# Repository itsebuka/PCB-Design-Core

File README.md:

# PCB Design Core

A central portfolio repository housing PCB design files, schematic captures, and embedded hardware prototypes. Projects range from custom microcontroller systems to specialized power management boards and discrete logic circuits.

---

## 🚀 Projects Overview

### 1. ESP32-S3 Test Board
* **Description:** Custom hardware evaluation platform designed around the ESP32-S3 microcontroller for IoT prototyping and wireless development.
* **Key Features:**
  * Clean power regulation network for stable MCU operation.
  * Dedicated break-out headers for GPIO, I2C, SPI, and UART peripherals.
  * Optimized 2-layer PCB layout with dedicated ground plane for RF/noise stability.
* **Directory:** [`/ESP32 S3 TESTBOARD`](./ESP32%20S3%20TESTBOARD)

---

### 2. LiPo Battery Charger PCB
* **Description:** Dedicated power management module for single-cell Lithium-Polymer (LiPo) battery charging and safety.
* **Key Features:**
  * Embedded charge controller IC with constant-current / constant-voltage (CC/CV) profile.
  * Built-in LED status indicators for charge state and fault monitoring.
  * Input voltage protection and compact surface-mount footprint.
* **Directory:** [`/LiPo Battery Charger PCB`](./LiPo%20Battery%20Charger%20PCB)

---

### 3. Magnitude Comparator PCB
* **Description:** Discrete hardware design focusing on digital logic arithmetic and signal processing.
* **Key Features:**
  * Multi-bit digital magnitude comparison logic.
  * Clean net labels and hierarchical layout organization.
  * Complete manufacturing outputs including Gerber files and drill charts.
* **Directory:** [`/Comparator-Project`](./Comparator-Project)

---

## 🛠️ Tools & Technologies

* **EDA Software:** KiCad 10.0 (Schematic Capture, PCB Layout, DRC/ERC)
* **Design Capabilities:** Multi-layer PCB routing, power plane isolation, custom footprint creation, DFM (Design for Manufacture).
* **Hardware Domain:** Embedded Microcontrollers (ESP32-S3), Power Management Systems, Signal Logic Circuits.
* **Version Control:** Git & GitHub Desktop.

---

## 📂 Repository Layout

```text
PCB-Design-Core/
├── ESP32 S3 TESTBOARD/        # ESP32-S3 hardware design files & schematics
├── LiPo Battery Charger PCB/  # Charger board layouts & manufacturing files
├── Comparator-Project/        # Magnitude comparator schematics & Gerber outputs
└── README.md                  # Central portfolio documentation

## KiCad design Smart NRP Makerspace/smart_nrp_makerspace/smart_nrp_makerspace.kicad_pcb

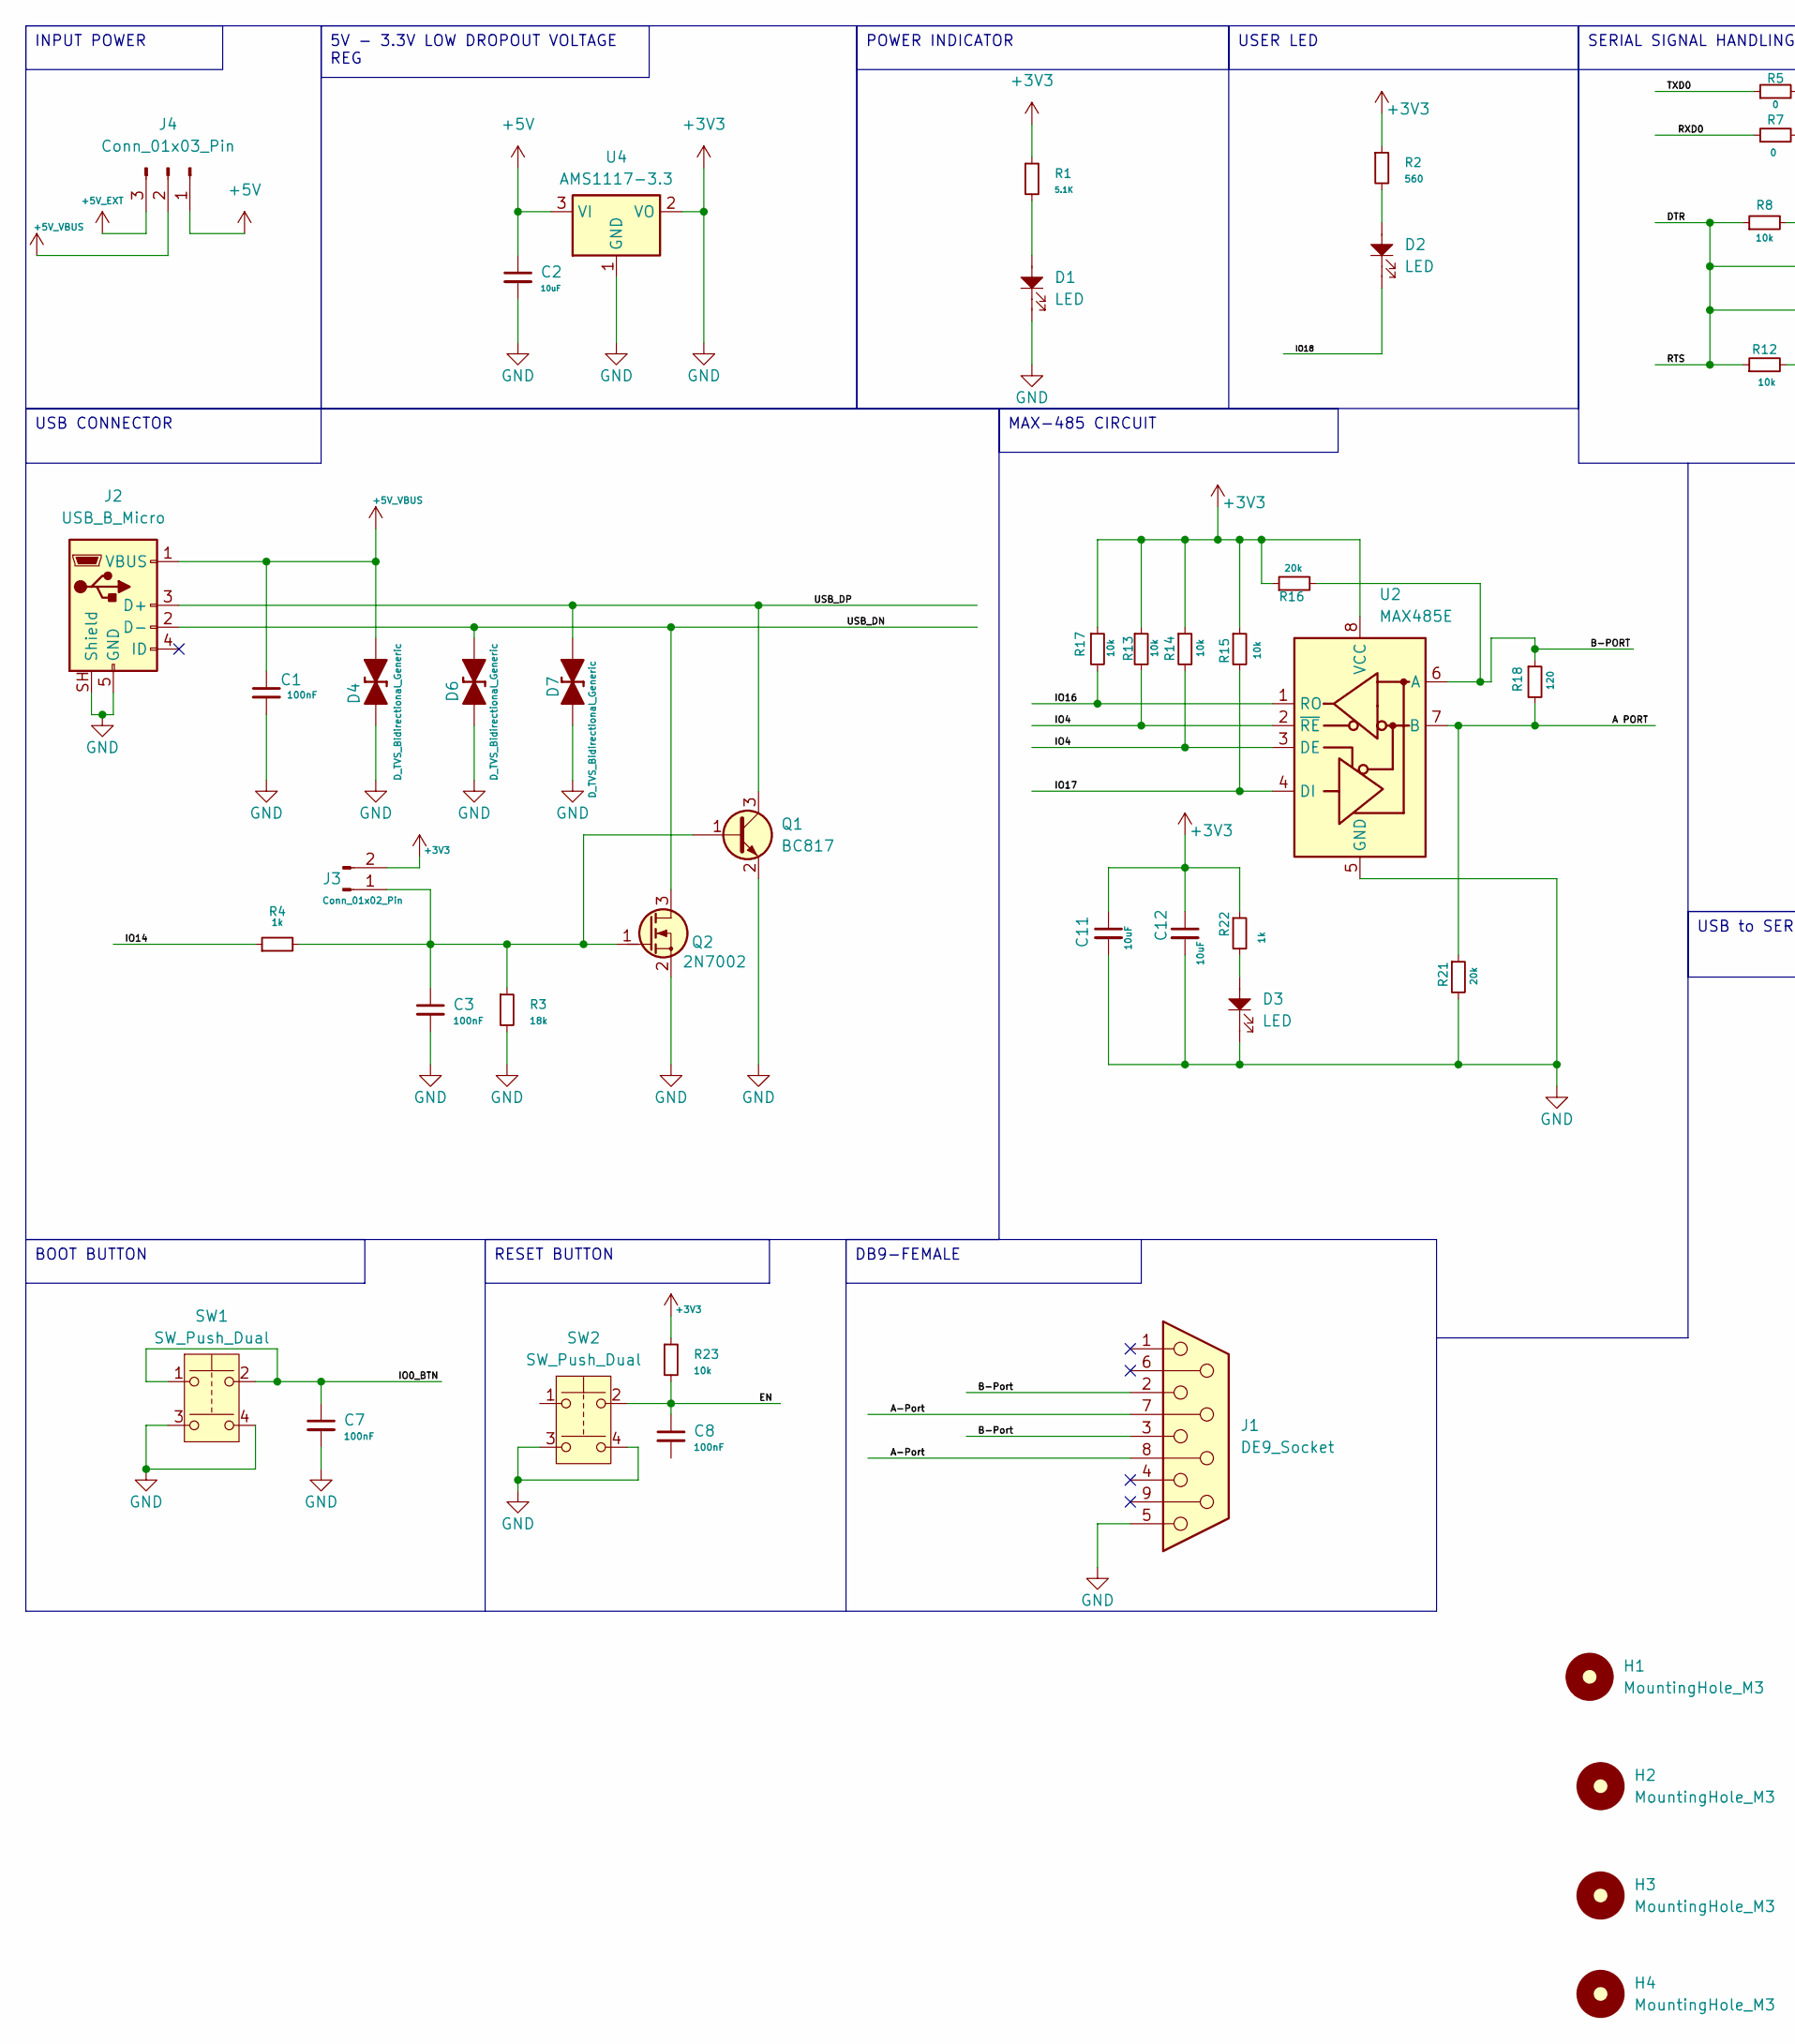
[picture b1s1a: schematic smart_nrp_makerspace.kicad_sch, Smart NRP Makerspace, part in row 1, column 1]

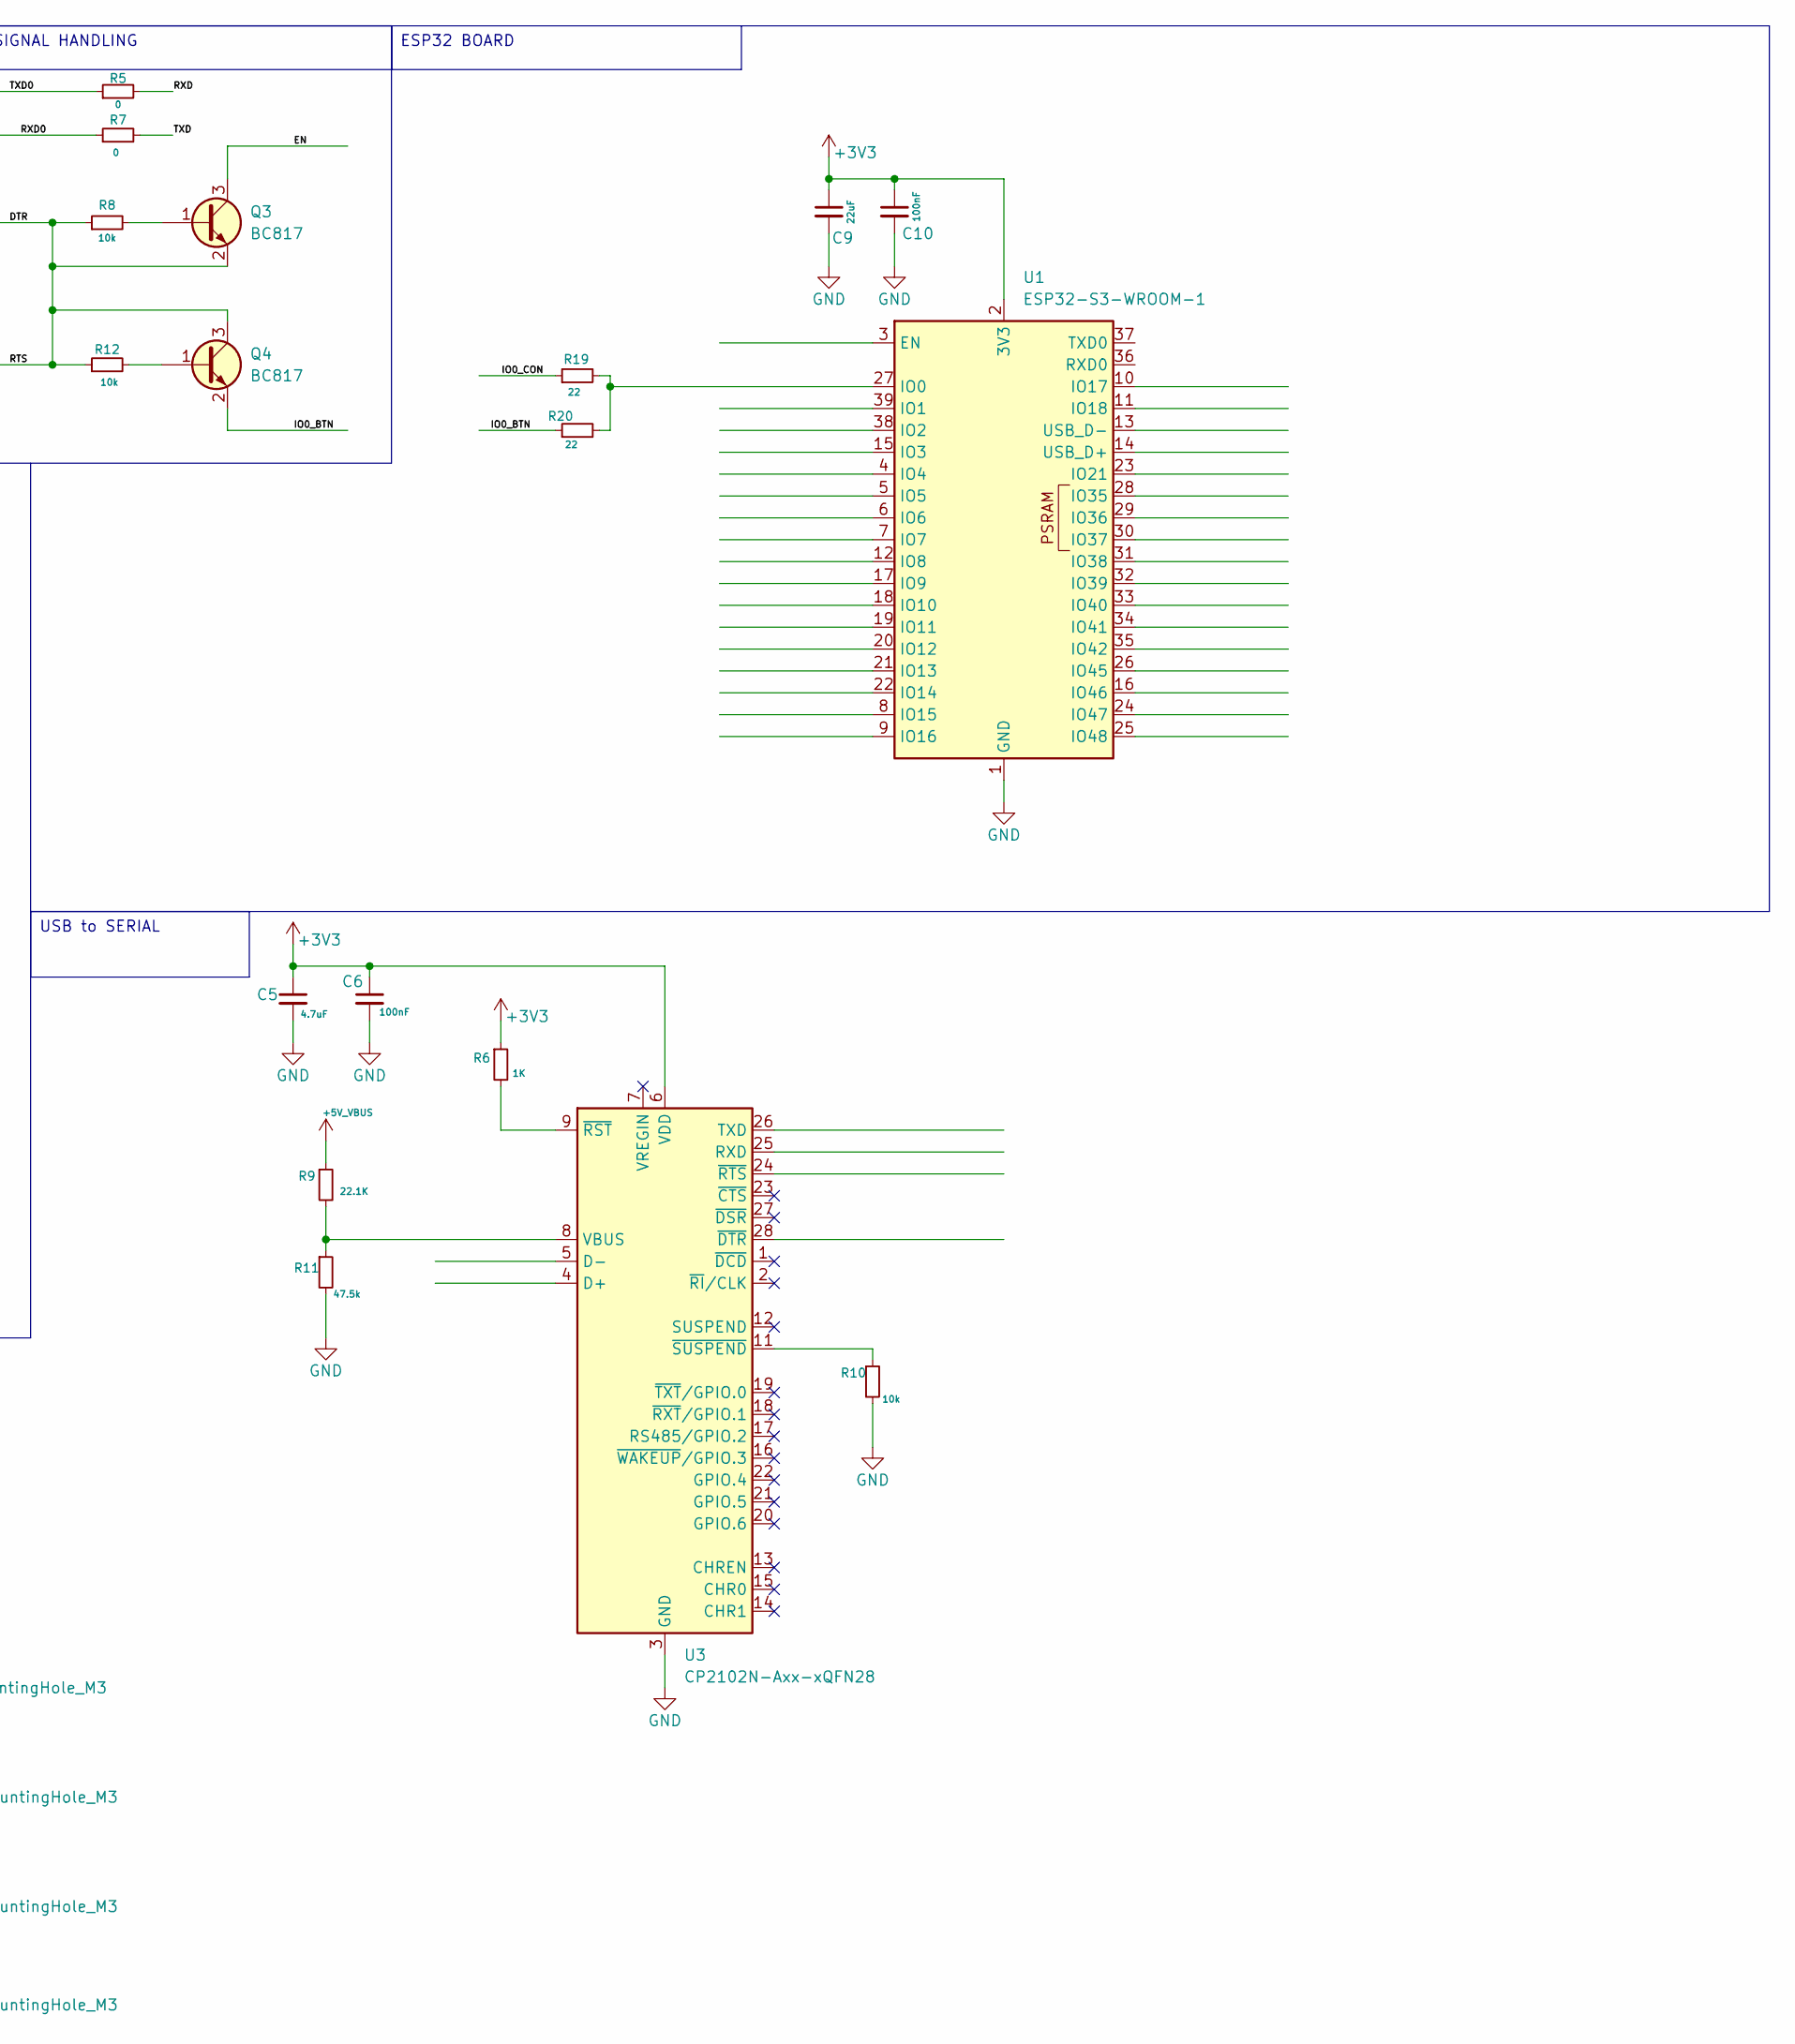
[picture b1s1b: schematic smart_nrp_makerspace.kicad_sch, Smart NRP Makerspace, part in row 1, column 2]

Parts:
C1, C3, C6, C7, C8, C10: 100nF; C_0402_1005Metric
C2, C11: 10uF; C_0402_1005Metric
C5: 4.7uF; C_0402_1005Metric
C9: 22uF; C_0805_2012Metric
C12: 10uF; C_0603_1608Metric
D1, D2, D3: LED; LED_D5.0mm
D4, D6, D7: D_TVS_Bidirectional_Generic; D_DO-214AC_SMA
H1, H2, H3, H4: MountingHole_M3; MountingHole_3.2mm_M3
J1: DE9_Socket; DSUB-9_Pins_Horizontal_P2.77x2.84mm_EdgePinOffset4.94mm_Hou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
J2: USB_B_Micro; USB_Micro-B_Molex-105017-0001
J3: Conn_01x02_Pin; PinHeader_1x02_P1.27mm_Vertical
J4: Conn_01x03_Pin; PinHeader_1x03_P2.54mm_Vertical
Q1, Q3, Q4: BC817; SOT-23
Q2: 2N7002; SOT-23
R1: 5.1K; R_0402
R2: 560; R_0402
R3: 18k; R_0402
R4, R22: 1k; R_0402
R5, R7: 0; R_0402
R6: 1K; R_0402
R8, R10, R12, R23: 10k; R_0402
R9: 22.1K; R_0402
R11: 47.5k; R_0402
R13, R14, R15, R17: 10k; R_0603_1608Metric
R16, R21: 20k; R_0603_1608Metric
R18: 120; R_0603_1608Metric
R19, R20: 22; R_0402
SW1, SW2: SW_Push_Dual; SW_Push_1P1T_NO_E-Switch_TL3301NxxxxxG
U1: ESP32-S3-WROOM-1
U2: MAX485E; SOIC-8_3.9x4.9mm_P1.27mm
U3: CP2102N-Axx-xQFN28; QFN-28-1EP_5x5mm_P0.5mm_EP3.35x3.35mm
U4: AMS1117-3.3; SOT-223-3_TabPin2

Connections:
+3V3: C1.2, C2.2, C3.2, C5.1, C5.2, C6.1, C6.2, C7.2, C9.1, C9.2, C10.1, C10.2, C11.1, C11.2, C12.1, C12.2, D1.1, D3.1, D4.1 (K), D6.1 (K), D7.1 (K), J1.5, J2.5 (GND), J2.SH (Shield), J3.2, Q1.2 (E), Q2.2 (S), R1.1, R2.1, R3.2, R6.1, R10.2, R11.2, R13.1, R14.1, R15.1, R16.1, R17.1, R21.2, R22.1, R23.1, SW1.3, SW1.4, SW2.3, SW2.4, U1.1 (GND), U1.2 (3V3), U1.40 (GND), U1.41 (GND), U2.5 (GND), U2.8 (VCC), U3.3 (GND), U3.6 (VDD), U3.29 (GND), U4.1 (GND), U4.2 (VO)
+5V: C2.1, J4.1, U4.3 (VI)
+5V_EXT: J4.3
+5V_VBUS: C1.1, D4.2 (A), J2.1 (VBUS), J4.2, R9.1
/A PORT: R18.2, R21.1, U2.7 (B)
/A-Port: J1.7, J1.8
/B-PORT: R16.2, R18.1, U2.6 (A)
/B-Port: J1.2, J1.3
/DTR: Q3.2 (E), Q4.3 (C), R8.1, R12.1
/EN: C8.1, Q3.3 (C), R23.2, SW2.2 (2_2)
/IO0_BTN: C7.1, Q4.2 (E), R20.1, SW1.1, SW1.2
/IO0_CON: R19.1
/IO4: R13.2, R14.2, U2.2 (~RE), U2.3 (DE)
/IO14: R4.1
/IO16: R17.2, U2.1 (RO)
/IO17: R15.2, U2.4 (DI)
/IO18: D2.1
/RXD: R5.2
/RXD0: R7.1
/TXD: R7.2
/TXD0: R5.1
/USB_DN: D6.2 (A), J2.2 (D-), Q2.3 (D)
/USB_DP: D7.2 (A), J2.3 (D+), Q1.3 (C)
unnamed: D1.2, R1.2
unnamed: D2.2, R2.2
unnamed: D3.2, R22.2
unnamed: C3.1, J3.1, Q1.1 (B), Q2.1 (G), R3.1, R4.2
unnamed: Q3.1 (B), R8.2
unnamed: Q4.1 (B), R12.2
unnamed: R19.2, R20.2, U1.27 (IO0)
unnamed: R9.2, R11.1, U3.8 (VBUS)
unnamed: R6.2, U3.9 (~RST)
unnamed: R10.1, U3.11 (~SUSPEND)

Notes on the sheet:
USB to SERIAL
DB9-FEMALE
POWER INDICATOR
BOOT BUTTON
ESP32 BOARD
5V - 3.3V LOW DROPOUT VOLTAGE REG
RESET BUTTON
USER LED
MAX-485 CIRCUIT
INPUT POWER
USB CONNECTOR
SERIAL SIGNAL HANDLING

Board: 4 copper layers, 58 parts (0 on the bottom side), 25 nets, no tracks yet.

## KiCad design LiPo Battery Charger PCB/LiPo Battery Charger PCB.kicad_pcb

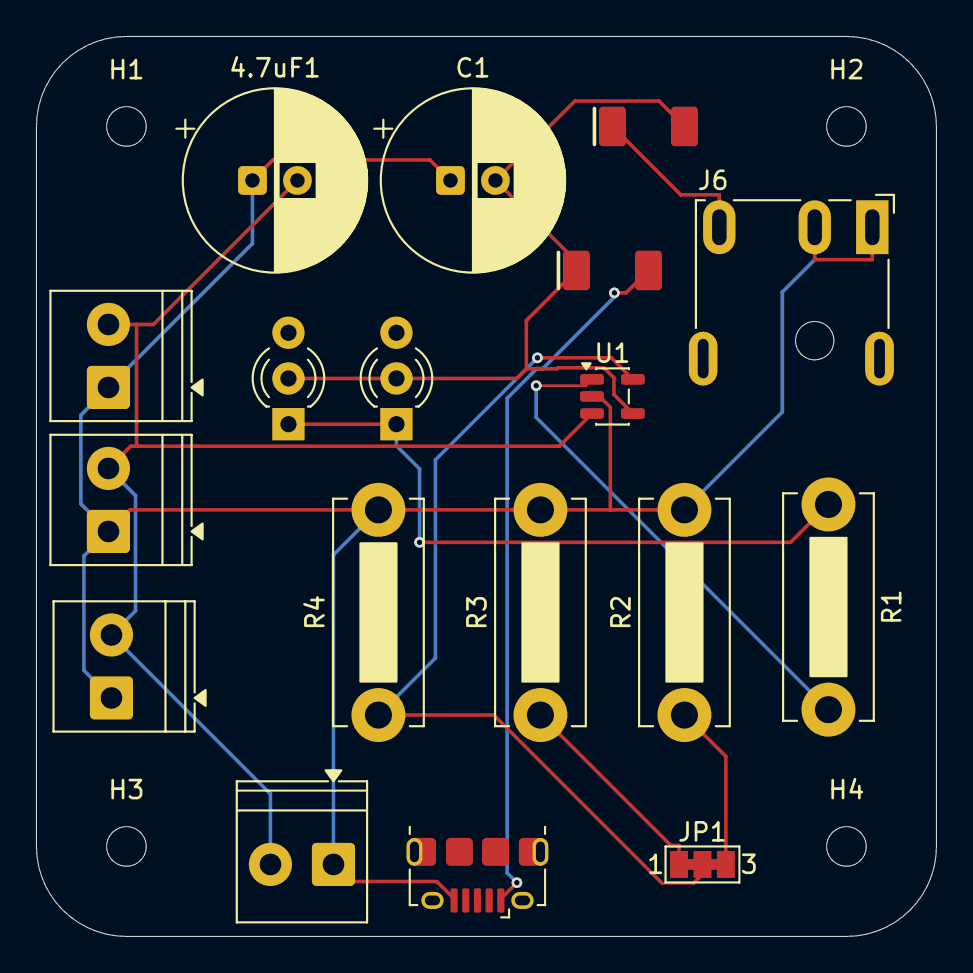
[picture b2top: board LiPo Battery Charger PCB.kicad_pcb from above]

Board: 2 copper layers, 50.0 x 50.0 mm, 22 parts (0 on the bottom side), 10 nets.

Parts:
4.7uF1: CP_Radial_D10.0mm_P2.50mm
40V,1ADiode1: SS14; SMA
C1: CP_Radial_D10.0mm_P2.50mm
D1, D2: Red; LED_D3.0mm-3
D3: SS14; SMA
H1, H2, H3, H4: MountingHole; MountingHole_2.2mm_M2
J1: USB_B_Micro; USB_Micro-B_Amphenol_10118194-0001LF_Horizontal
J2: Screw_Terminal_1; TerminalBlock_Phoenix_PT-1,5-2-3.5-H_1x02_P3.50mm_Horizontal
J3: Screw terminal 2; TerminalBlock_Phoenix_PT-1,5-2-3.5-H_1x02_P3.50mm_Horizontal
J4: Screw_Terminal_3; TerminalBlock_Phoenix_PT-1,5-2-3.5-H_1x02_P3.50mm_Horizontal
J5: Screw_Terminal_4; TerminalBlock_Phoenix_PT-1,5-2-3.5-H_1x02_P3.50mm_Horizontal
J6: Barrel_Jack_Switch; BarrelJack_CUI_PJ-079BH_Horizontal
JP1: SolderJumper; SolderJumper-3_P1.3mm_Bridged123_Pad1.0x1.5mm_NumberLabels
R1: 330; R_Bare_Metal_Element_L12.4mm_W4.8mm_P11.40mm
R2: 2k; R_Bare_Metal_Element_L12.4mm_W4.8mm_P11.40mm
R3: 10k; R_Bare_Metal_Element_L12.4mm_W4.8mm_P11.40mm
R4: 10K; R_Bare_Metal_Element_L12.4mm_W4.8mm_P11.40mm
U1: Battery controller; SOT-23-5

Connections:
GND: 4.7uF1.1, C1.1, J1.5 (GND), J2.1, J3.1, J4.1, J5.1, J6.1, J6.3, R2.2, R3.2, R4.2, U1.2 (V_{SS})
unnamed: 40V,1ADiode1.2 (A), C1.2, D1.2 (A), D2.2 (A), D3.1 (K), U1.4 (V_{DD})
unnamed: 40V,1ADiode1.1 (K), J6.2
unnamed: D1.1 (K), D2.1 (K), R1.1
unnamed: D3.2 (A), J1.1 (VBUS)
unnamed: JP1.1 (A), R3.1
unnamed: JP1.3 (B), R2.1
unnamed: JP1.2 (C), R4.1, U1.5 (PROG)
unnamed: R1.2, U1.1 (CE)
unnamed: 4.7uF1.2, J2.2, J3.2, J4.2, J5.2, U1.3 (V_{BAT})

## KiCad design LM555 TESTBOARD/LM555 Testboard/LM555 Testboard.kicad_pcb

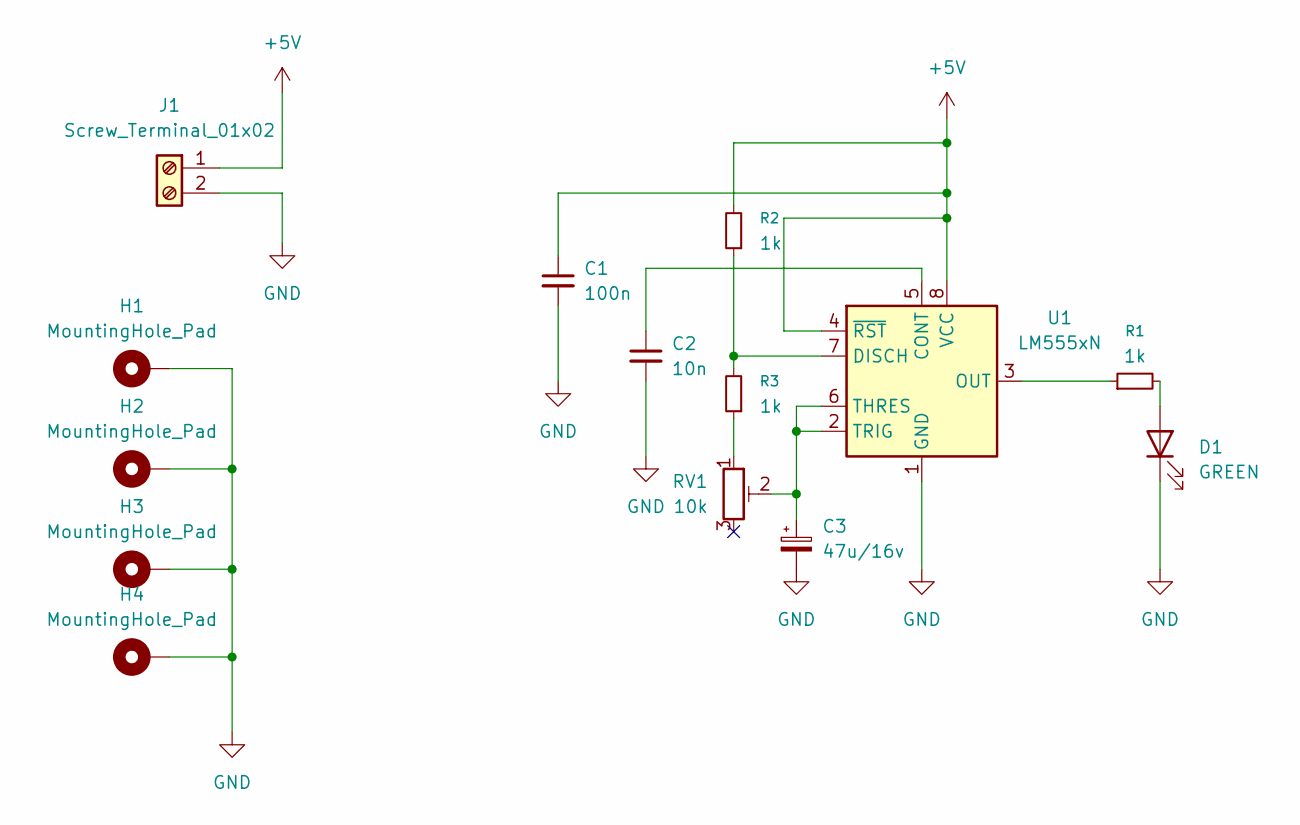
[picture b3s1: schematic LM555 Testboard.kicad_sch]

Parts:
C1: 100n; C_Disc_D7.0mm_W2.5mm_P5.00mm
C2: 10n; C_Disc_D7.0mm_W2.5mm_P5.00mm
C3: 47u/16v; CP_Radial_D10.0mm_P2.50mm
D1: GREEN; LED_D3.0mm
H1, H2, H3, H4: MountingHole_Pad; MountingHole_3.2mm_M3_DIN965_Pad
J1: Screw_Terminal_01x02; TerminalBlock_Phoenix_PT-1,5-2-5.0-H_1x02_P5.00mm_Horizontal
R1, R2, R3: 1k; R_Axial_DIN0207_L6.3mm_D2.5mm_P10.16mm_Horizontal
RV1: 10k; Potentiometer_Bourns_3386P_Vertical
U1: LM555xN; DIP-8_W7.62mm

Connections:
+5V: C1.1, J1.1, R2.2, U1.4 (~RST), U1.8 (VCC)
GND: C1.2, C2.2, C3.2, D1.1 (K), H1.1 (1_1), H2.1 (1_1), H3.1 (1_1), H4.1 (1_1), J1.2, U1.1 (GND)
unnamed: D1.2 (A), R1.2
unnamed: R3.1, RV1.1
unnamed: C2.1, U1.5 (CONT)
unnamed: R2.1, R3.2, U1.7 (DISCH)
unnamed: R1.1, U1.3 (OUT)
unnamed: C3.1, RV1.2, U1.2 (TRIG), U1.6 (THRES)

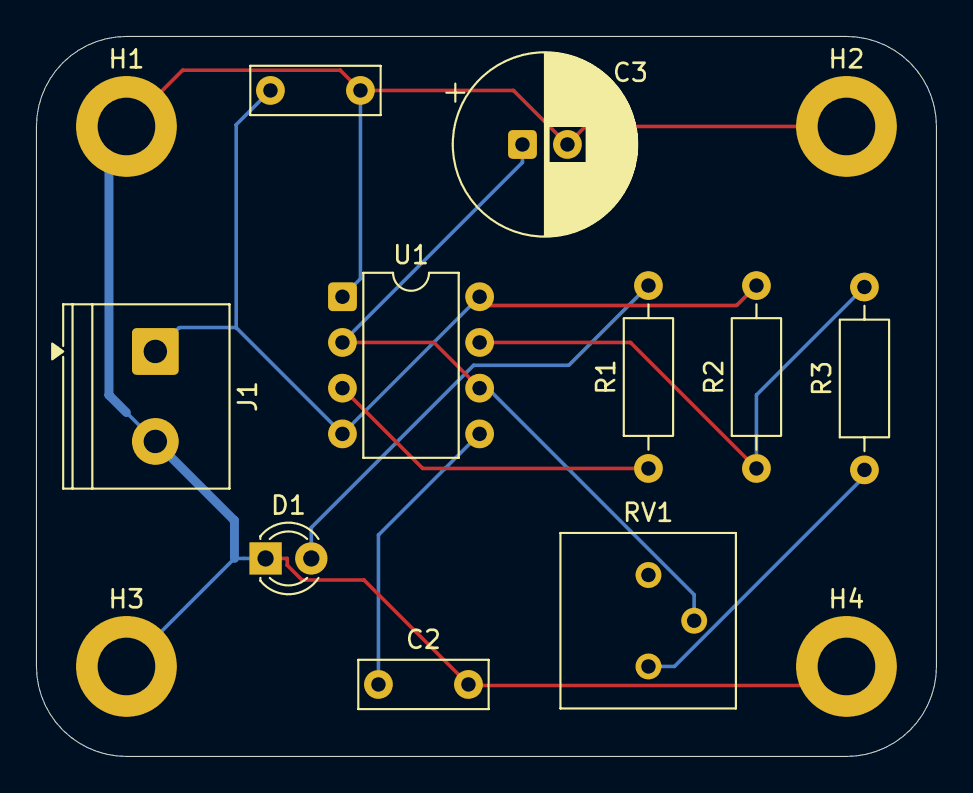
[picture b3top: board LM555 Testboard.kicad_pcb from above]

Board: 2 copper layers, 50.0 x 40.0 mm, 14 parts (0 on the bottom side), 8 nets.
